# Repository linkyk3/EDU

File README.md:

Projects from my Bachelor and Master Industrial Sciences at the VUB

## 3rd Bachelor:
### Databanken en Webtechnologie - Attendences Register Website
For the project of this course we had to design an application in the form of a website for registering attendences of different courses and subjects. The application includes a database, RESTful API and the site's frontend. SQLite is used for the database, Python for the backend and HTML/CSS for the frontend.

### Bachelorthesis - Roboball
As assignment we had to design and build a spherical robot that could move by modulating its mass. A well known example is the [Sphero](https://sphero.com/blogs/news/what-is-sphero) that uses a small, wheeled robot inside a shell that climbs up the walls and pushes them forward, causing the ball to roll. We were not allowed to copy this mechanism. These were the only design constrains that were given. We opted for an alternative method that used servo motors to control the rotation of the robot as well as the modulation of the mass, causing the robot to roll. In the report, all our design decisions, implementations and tests are explained.

## 1st Master:
### Computerarchitectuur - MIPS with UART Implementation in VHDL
In this project we implemented a basic MIPS processor in VHDL. The MIPS had to support the [core instruction set](https://inst.eecs.berkeley.edu/~cs61c/resources/MIPS_Green_Sheet.pdf). This allows the MIPS to run basic C programs like for loops, if statements, function calls, etc. A special feature also had to be present. We chose UART communication using Memory Mapped IO.

### Transmissietechnieken en Multimedia - MIVB/STIB Control App
For the multimedia part of this course we had to develop an Android app. [Back in 2014](https://www.nieuwsblad.be/cnt/dmf20140905_01252657) there was a popular app that allowed users to signal if there was a control happening at specific stops of the Brussels public transport system. This app was shut down a few years later. For this project we remade this app from scratch. The app uses the GPS of your phone to track the nearby stations and indicated if there is a control happening at the station. A Google Firestore database is used to save the stations where a control is happening so that the real-time data is available for multiple users. 

### Embedded DSP - Beamforming Simulation in Matlab and implementation in VHDL

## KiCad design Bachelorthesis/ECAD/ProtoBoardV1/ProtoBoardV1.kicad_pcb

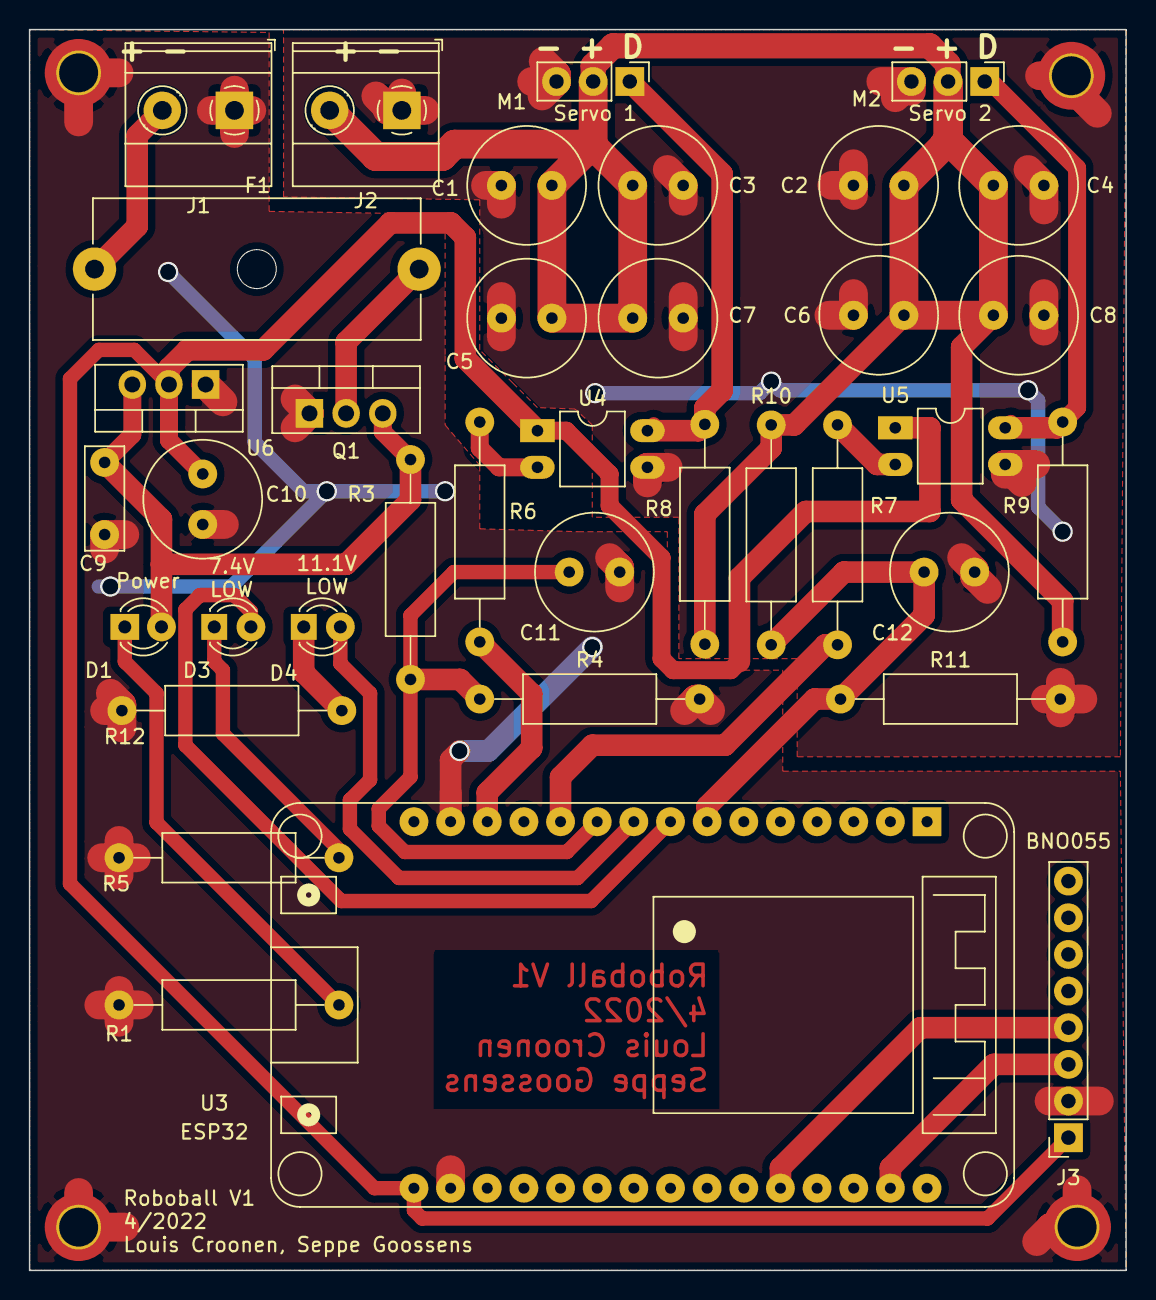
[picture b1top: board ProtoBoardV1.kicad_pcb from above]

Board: 2 copper layers, 76.0 x 86.0 mm, 41 parts (0 on the bottom side), 22 nets.

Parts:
C1, C2, C3, C4, C5, C6, C7, C8: 220uF; C_Radial_D8.0mm_H11.5mm_P3.50mm
C9: 100nF; C_Disc_D7.0mm_W2.5mm_P5.00mm
C10: 10uF; C_Radial_D8.0mm_H11.5mm_P3.50mm
C11, C12: 100nF; C_Radial_D8.0mm_H11.5mm_P3.50mm
D1, D3, D4: LED; LED_D3.0mm_Clear
F1: Fuse; Fuseholder_Cylinder-5x20mm_Schurter_0031_8201_Horizontal_Op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
J1, J2: TerminalBlock_Phoenix_MKDS-1,5-2_1x02_P5.00mm_Hor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; TerminalBlock_Phoenix_MKDS-1,5-2_1x02_P5.00mm_Horizontal
J3: BNO055; PinSocket_1x08_P2.54mm_Vertical
M1: Servo 1; PinHeader_1x03_P2.54mm_Vertical
M2: Servo 2; PinHeader_1x03_P2.54mm_Vertical
M_Hole1, M_Hole2, M_Hole3, M_Hole4: MountingHole_2.7mm_M2.5_DIN965_Pad_TopOnly
Q1: IRF9540N; TO-220-3_Vertical
R1, R5, R12: 720; R_Axial_DIN0309_L9.0mm_D3.2mm_P15.24mm_Horizontal
R3, R10: 2.7M; R_Axial_DIN0309_L9.0mm_D3.2mm_P15.24mm_Horizontal
R4: 2.2M; R_Axial_DIN0309_L9.0mm_D3.2mm_P15.24mm_Horizontal
R6, R7: 470; R_Axial_DIN0309_L9.0mm_D3.2mm_P15.24mm_Horizontal
R8, R9: 1.2k; R_Axial_DIN0309_L9.0mm_D3.2mm_P15.24mm_Horizontal
R11: 3.3M; R_Axial_DIN0309_L9.0mm_D3.2mm_P15.24mm_Horizontal
U3: ESP32_DevKit_V1_DOIT; esp32_devkit_v1_doit
U4, U5: FOD817C; DIP-4_W7.62mm_LongPads
U6: LD1117V33; TO-220-3_Vertical

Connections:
+3V3: C10.1, J3.1, U3.16, U4.1, U5.1, U6.2
+7.5V: C9.1, D1.2, Q1.3, R3.1, U6.3
/6V: C1.1, C2.1, C3.1, C4.1, C5.1, C6.1, C7.1, C8.1, J2.2, M1.2, M2.2, R8.1, R9.1, R10.1
/BATLVL_7.4: C11.1, R3.2, R4.1, U3.10
/BATLVL_11.1: C12.1, R10.2, R11.1, U3.7
/LVL_LED_7.4: D3.2, U3.8
/LVL_LED_11.1: D4.2, U3.9
/SCL: J3.3, U3.29
/SDA: J3.4, U3.26
/Servo1: R6.2, U3.13
/Servo1_DPIN: M1.1, R8.2, U4.4
/Servo2: R7.2, U3.11
/Servo2_DPIN: M2.1, R9.2, U5.4
GND: C9.2, C10.2, C11.2, J1.1, J3.2, M_Hole1.1, M_Hole3.1, M_Hole4.1, Q1.1, R1.1, R4.2, R5.1, R12.1, U3.14, U3.17, U6.1
GND2: C1.2, C2.2, C3.2, C4.2, C5.2, C6.2, C7.2, C8.2, C12.2, J2.1, M1.3, M2.3, M_Hole2.1, R11.2, U4.3, U5.3
unnamed: D1.1, R1.2
unnamed: D3.1, R5.2
unnamed: D4.1, R12.2
unnamed: F1.1, Q1.2
unnamed: F1.2, J1.2
unnamed: R6.1, U4.2
unnamed: R7.1, U5.2

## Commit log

2023-02-14 multimedia report
2023-05-03 Beamforming VHDL
2023-05-03 changed location
